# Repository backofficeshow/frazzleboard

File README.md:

# frazzleboard
Muti output retro computer linear PSU

The idea of this board is a general linear PSU for retro computers

It should be ok for audio applications, please check the required capacitor values.

Thanks to everyone on the stream and the James Bearss for checking out the design.

It shouldnt electrocute you, but it might, so be safe and be aware of the risks!

Lots of Love

Dr A!

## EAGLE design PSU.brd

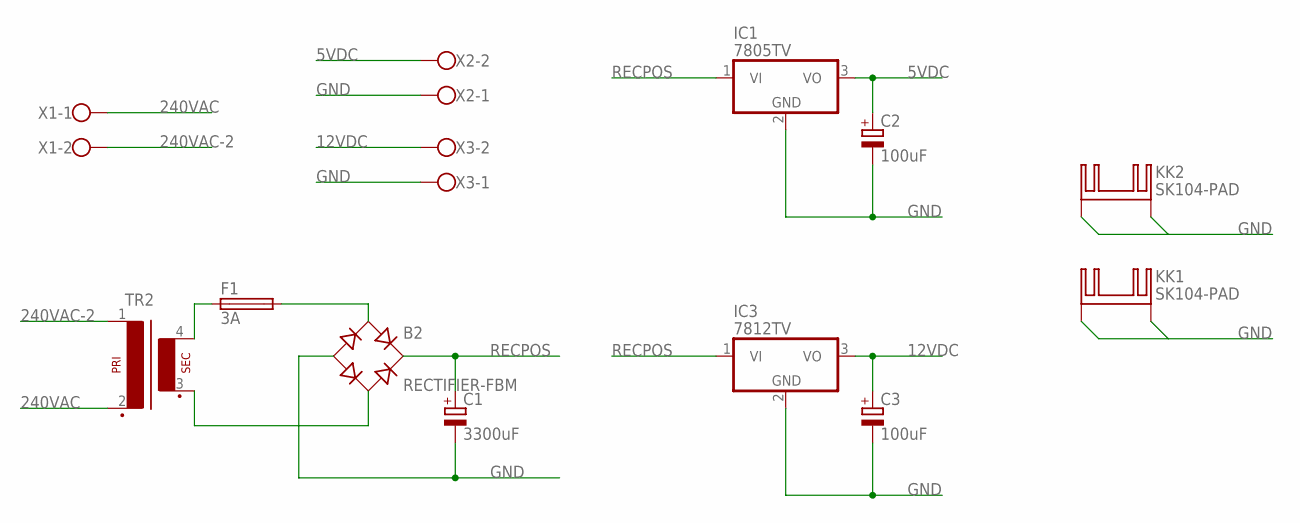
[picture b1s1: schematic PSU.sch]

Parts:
B2: RECTIFIER-FBM; FBM
C1: 3300uF; EB35D
C2, C3: 100uF; E5-10,5
F1: 3A; SH25
IC1: 7805TV; TO220V
IC3: 7812TV; TO220V
KK1, KK2: SK104-PAD
TR2: VP31
X1, X2, X3: W237-102

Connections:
5VDC: C2.+, IC1.3 (VO), X2.2
12VDC: C3.+, IC3.3 (VO), X3.2
240VAC: TR2.2, X1.1
240VAC-2: TR2.1, X1.2
GND: B2.-, C1.-, C2.-, C3.-, IC1.2 (GND), IC3.2 (GND), KK1.K1, KK1.K2, KK2.K1, KK2.K2, X2.1, X3.1
unnamed: F1.1, TR2.4 (S4)
unnamed: B2.AC2, TR2.3 (S3)
unnamed: B2.AC1, F1.2
RECPOS: B2.+, C1.+, IC1.1 (VI), IC3.1 (VI)

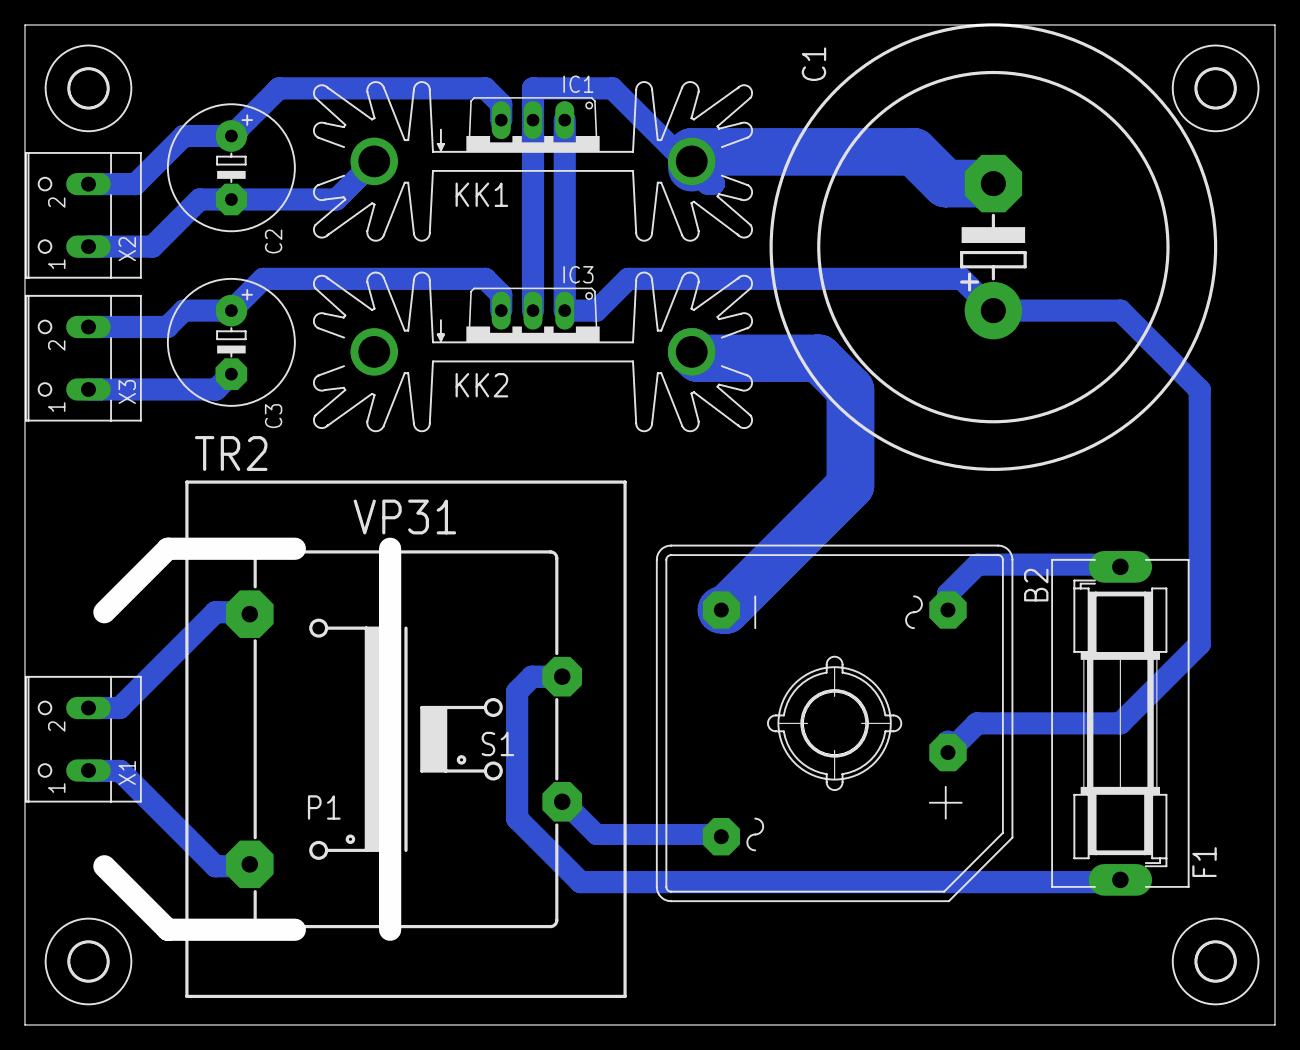
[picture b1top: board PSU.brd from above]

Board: 2 copper layers, 100.0 x 80.0 mm, 18 parts (0 on the bottom side), 9 nets.

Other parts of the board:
U$1, U$2, U$3, U$4: 3,0
U$5: 5,0

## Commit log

2018-10-20 Frazzle board version 1
    Untested, unproven, probably dangerous! Refer to the stream for more.

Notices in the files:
PSU.brd:
(c)2018 Dr Andy's
